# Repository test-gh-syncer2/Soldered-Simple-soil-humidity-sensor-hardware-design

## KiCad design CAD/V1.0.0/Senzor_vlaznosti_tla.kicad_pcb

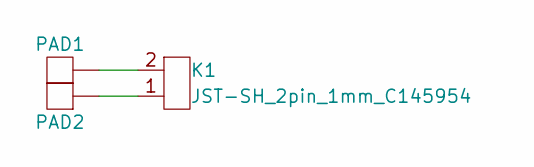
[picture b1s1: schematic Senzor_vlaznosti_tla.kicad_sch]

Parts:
K1: JST-SH_2pin_1mm_C145954
PAD1, PAD2: PAD_2x1.5

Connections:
unnamed: K1.1, PAD2.1
unnamed: K1.2, PAD1.1

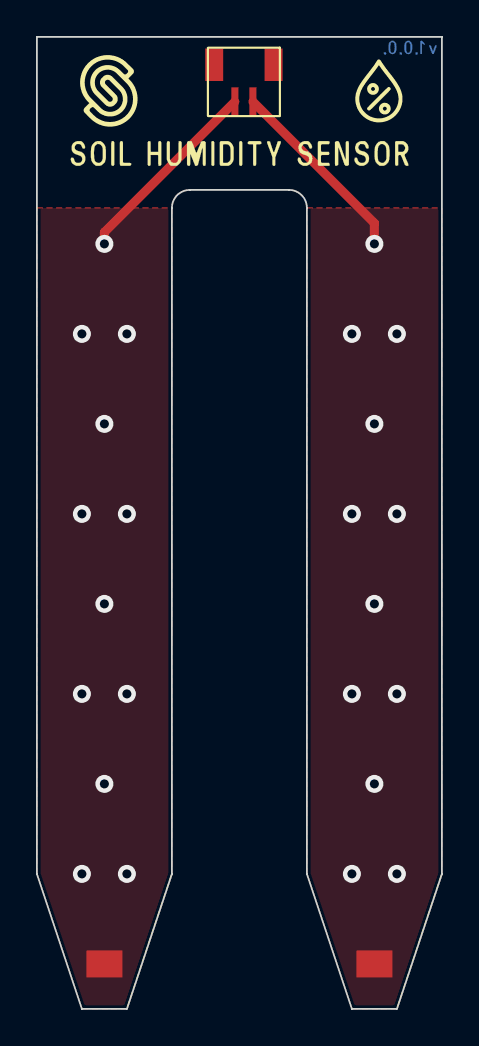
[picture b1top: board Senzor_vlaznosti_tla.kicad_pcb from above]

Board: 2 copper layers, 22.5 x 54.0 mm, 3 parts (0 on the bottom side), 2 nets.

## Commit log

2021-09-23 Syncing to git
2021-09-23 Updating open source files.
